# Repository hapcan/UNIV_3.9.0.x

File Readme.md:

UNIV 3.9.0.x
============

OPEN COLLECTOR OUTPUTS - Isolated 10 channel NPN open collector outputs with clamp diodes, 24V, 500mA per channel

Device webpage: http://hapcan.com/devices/universal/univ_3/univ_3-9-0-x/

Hardware created in Eagle PCB Software http://www.cadsoftusa.com/

Firmware created in Microchip MPLAB http://www.microchip.com/mplabide/ in assembly language

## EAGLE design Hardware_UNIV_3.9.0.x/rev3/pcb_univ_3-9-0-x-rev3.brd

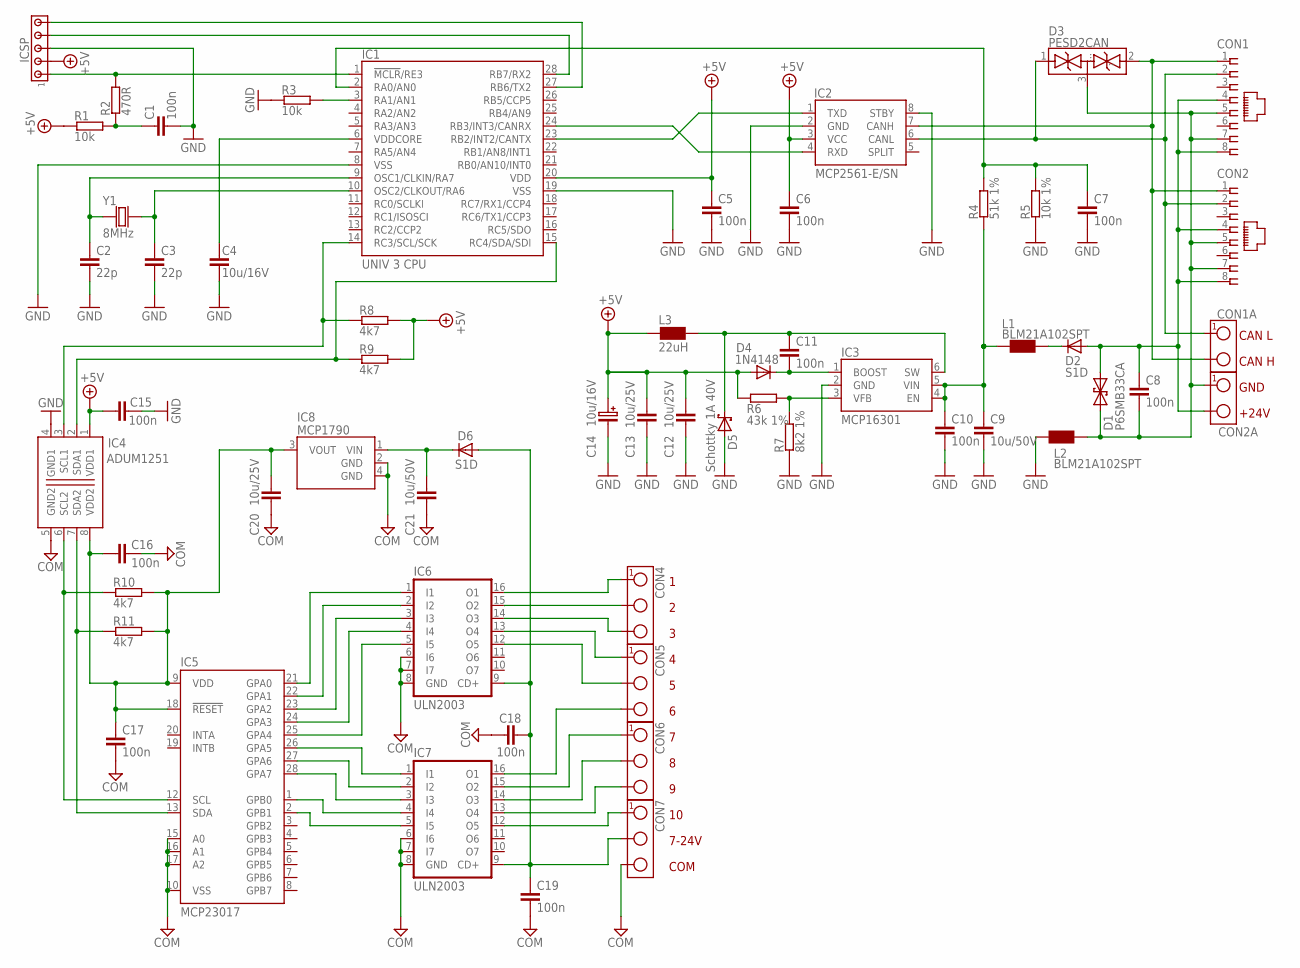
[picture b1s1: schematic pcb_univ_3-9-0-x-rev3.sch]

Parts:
C1, C5, C6, C7, C8, C10, C11, C15, C16, C17, C18, C19: 100n; 0805
C2, C3: 22p; 0805
C4: 10u/16V; 0805
C9, C21: 10u/50V; 1210
C12, C13, C20: 10u/25V; 1206
C14: 10u/16V; SMC_B
CON1, CON2: RJ45-SOCKET; RJ45-PCB-SOCKET
CON1A, CON2A: TERMINAL-2; ARK2-5X10,5MM
CON4, CON5, CON6, CON7: TERMINAL-3-3.81X8MM; ARK3-3.81X8MM
D1: P6SMB33CA; DO-214_TRANSIL2
D2, D6: S1D; DO-214
D3: PESD2CAN; SOT-23
D4: 1N4148; 0805
D5: Schottky 1A 40V; DO-214
IC1: UNIV 3 CPU; UNIV3CPU
IC2: MCP2561-E/SN; SO-08
IC3: MCP16301; SOT-23-6
IC4: ADUM1251; SO-08
IC5: MCP23017; SO-28W
IC6, IC7: ULN2003; SO-16
IC8: MCP1790; SOT-223
ICSP: HEADER5; SIP-5
L1, L2: BLM21A102SPT; 0805
L3: 22uH; CHOKE-DER0705
R1, R3: 10k; 0805
R2: 470R; 0805
R4: 51k 1%; 0805
R5: 10k 1%; 0805
R6: 43k 1%; 0805
R7: 8k2 1%; 0805
R8, R9, R10, R11: 4k7; 0805
Y1: 8MHz; CRYSTAL-HC49V

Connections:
+5V: C5.1, C6.1, C12.1, C13.1, C14.+ (1), C15.1, D4.2 (A), IC1.20 (VDD), IC2.3 (VCC), IC4.1 (VDD1), ICSP.2, L3.1, R1.1, R6.1, R8.2, R9.2
GND: C1.2, C2.2, C3.2, C4.2, C5.2, C6.2, C7.2, C9.2, C10.2, C12.2, C13.2, C14.- (2), C15.2, D5.A, IC1.8 (VSS), IC1.19 (VSS), IC2.2 (GND), IC2.8 (STBY), IC3.2 (GND), IC4.4 (GND1), ICSP.3, L2.1, R3.1, R5.1, R7.1
GND1: C16.2, C17.2, C18.1, C19.1, C20.2, C21.2, CON7.3, IC4.5 (GND2), IC5.10 (VSS), IC5.15 (A0), IC5.16 (A1), IC5.17 (A2), IC6.6 (I6), IC6.7 (I7), IC6.8 (GND), IC7.6 (I6), IC7.7 (I7), IC7.8 (GND), IC8.2 (GND), IC8.4 (GND)
unnamed: D2.C, L1.2
unnamed: IC1.24 (RB3/INT3/CANRX), IC2.4 (RXD)
unnamed: IC1.23 (RB2/INT2/CANTX), IC2.1 (TXD)
unnamed: CON1.1, CON1A.2, CON2.1, D3.2 (..), IC2.7 (CANH)
unnamed: C9.1, C10.1, IC3.4 (EN), IC3.5 (VIN), L1.1, R4.1
unnamed: CON4.1, IC6.16 (O1)
unnamed: C1.1, R1.2, R2.1
unnamed: IC1.1 (!MCLR!/RE3), ICSP.1, R2.2
unnamed: C8.1, CON1.4, CON1.8, CON2.4, CON2.8, CON2A.2, D1.C (2), D2.A
unnamed: IC1.28 (RB7/RX2), ICSP.4
unnamed: CON4.2, IC6.15 (O2)
unnamed: IC1.3 (RA1/AN1), R3.2
unnamed: C8.2, CON1.5, CON1.7, CON2.5, CON2.7, CON2A.1, D1.A (1), D3.3 (...), L2.2
unnamed: IC1.27 (RB6/TX2), ICSP.5
unnamed: C3.1, IC1.10 (OSC2/CLKOUT/RA6), Y1.2
unnamed: C7.1, IC1.2 (RA0/AN0), R4.2, R5.2
unnamed: C11.1, D5.C, IC3.6 (SW), L3.2
unnamed: CON4.3, IC6.14 (O3)
unnamed: CON5.1, IC6.13 (O4)
unnamed: IC3.3 (VFB), R6.2, R7.2
unnamed: CON5.2, IC6.12 (O5)
unnamed: C16.1, C17.1, C20.1, IC4.8 (VDD2), IC5.9 (VDD), IC5.18 (!RESET), IC8.3 (VOUT), R10.2, R11.2
unnamed: C21.1, D6.C, IC8.1 (VIN)
unnamed: CON5.3, IC7.16 (O1)
unnamed: CON6.1, IC7.15 (O2)
unnamed: CON1.2, CON1A.1, CON2.2, D3.1 (.), IC2.6 (CANL)
unnamed: CON6.3, IC7.13 (O4)
unnamed: CON7.1, IC7.12 (O5)
unnamed: CON6.2, IC7.14 (O3)
unnamed: C18.2, C19.2, CON7.2, D6.A, IC6.9 (CD+), IC7.9 (CD+)
unnamed: IC5.21 (GPA0), IC6.1 (I1)
unnamed: C11.2, D4.1 (C), IC3.1 (BOOST)
unnamed: IC5.22 (GPA1), IC6.2 (I2)
unnamed: C2.1, IC1.9 (OSC1/CLKIN/RA7), Y1.1
unnamed: IC5.23 (GPA2), IC6.3 (I3)
unnamed: IC5.24 (GPA3), IC6.4 (I4)
unnamed: IC5.25 (GPA4), IC6.5 (I5)
unnamed: IC5.26 (GPA5), IC7.1 (I1)
unnamed: IC5.27 (GPA6), IC7.2 (I2)
unnamed: IC5.28 (GPA7), IC7.3 (I3)
unnamed: IC5.1 (GPB0), IC7.4 (I4)
unnamed: IC5.2 (GPB1), IC7.5 (I5)
unnamed: IC4.6 (SCL2), IC5.12 (SCL), R10.1
unnamed: IC4.7 (SDA2), IC5.13 (SDA), R11.1
unnamed: C4.1, IC1.6 (VDDCORE)
unnamed: IC1.15 (RC4/SDA/SDI), IC4.2 (SDA1), R9.1
unnamed: IC1.14 (RC3/SCL/SCK), IC4.3 (SCL1), R8.1

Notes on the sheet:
CAN L
CAN H
GND
+24V
7-24V
COM

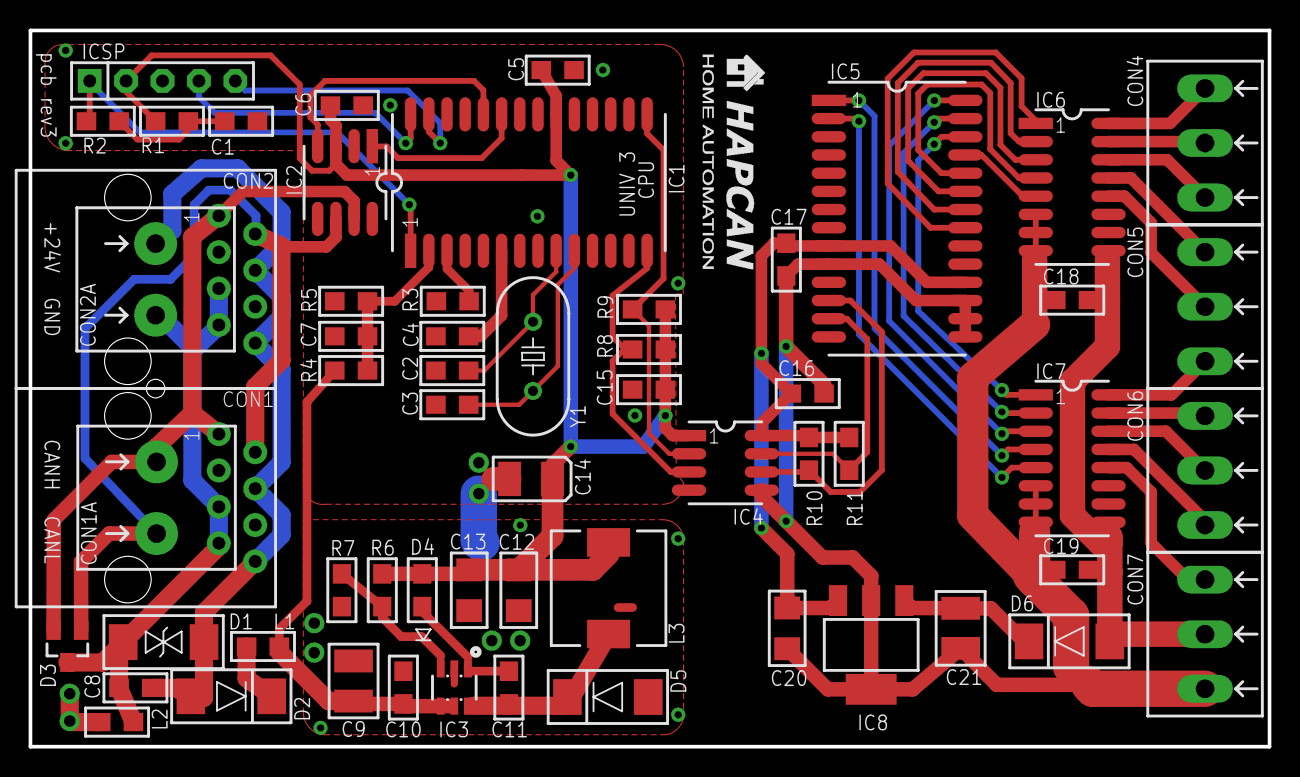
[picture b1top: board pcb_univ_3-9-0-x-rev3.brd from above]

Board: 2 copper layers, 86.5 x 50.0 mm, 59 parts (0 on the bottom side), 50 nets.

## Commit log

2018-04-28 :boom::camel: Added .gitattributes & .gitignore files
2018-04-28 hardware UNIV 3.9.0.x revision 3
2018-04-28 hardware UNIV 3.9.0.0 revision 0
2018-04-30 firmware UNIV 3.9.0.0 revision 0
2022-11-15 firmware UNIV 3.9.0.0 revision 1
2022-11-15 MIT license
